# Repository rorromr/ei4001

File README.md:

# EI4001

## Torso lift mechanism

## Instalación

# Repositorio

```
git clone https://github.com/rorromr/ei4001.git
cd ei4001
git submodule init
git submodule update
```
# Librerías Arduino

Para la instalación de librerías se crean enlaces simbolicos en el directorio `~/Arduino/libraries/`.

```
cd ei4001/arduino
./install.sh

```

## Comandos Git

[Guía rápida Git](http://rogerdudler.github.io/git-guide/index.es.html)

### Commandos útiles

* Clonar repositorio: `git clone user@ip_server:repo`
* Crear rama: `git checkout -b nueva_rama`
* Listar ramas: `git branch -a`
* Bajar rama: `git pull origin nombre_rama`
* Crear rama local y setear track remoto: `git checkout -t origin/nombre_rama`
* Borrar rama local (-D para forzar): `git branch -d nombre_rama`
* Borrar rama remota: `git push origin :nombre-rama`
* Subir nueva rama con tracking: `git push -u origin rama`
* Actualizar lista de ramas: `git remote update origin --prune`
* Borrar rama local: `git branch -d rama`
* Borrar rama remota: `git push origin --delete rama`

## Markdown

* [Markdown basics](https://help.github.com/articles/markdown-basics/)
* [Mastering Markdown](https://guides.github.com/features/mastering-markdown/)

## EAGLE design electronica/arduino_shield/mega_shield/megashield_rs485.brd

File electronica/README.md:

# EI4001

## Torso lift mechanism

Archivos de diseño electrónico.

## Puente H

Puente H basado en MOSFET de potencia IRF2804 usando drivers
IR2110.

## Sitios web

* [Calculo de ancho de pistas](http://www.desmith.net/NMdS/Electronics/TraceWidth.html)
* [Ejemplos puente H](http://tahmidmc.blogspot.cl/2013/01/using-high-low-side-driver-ir2110-with.html)

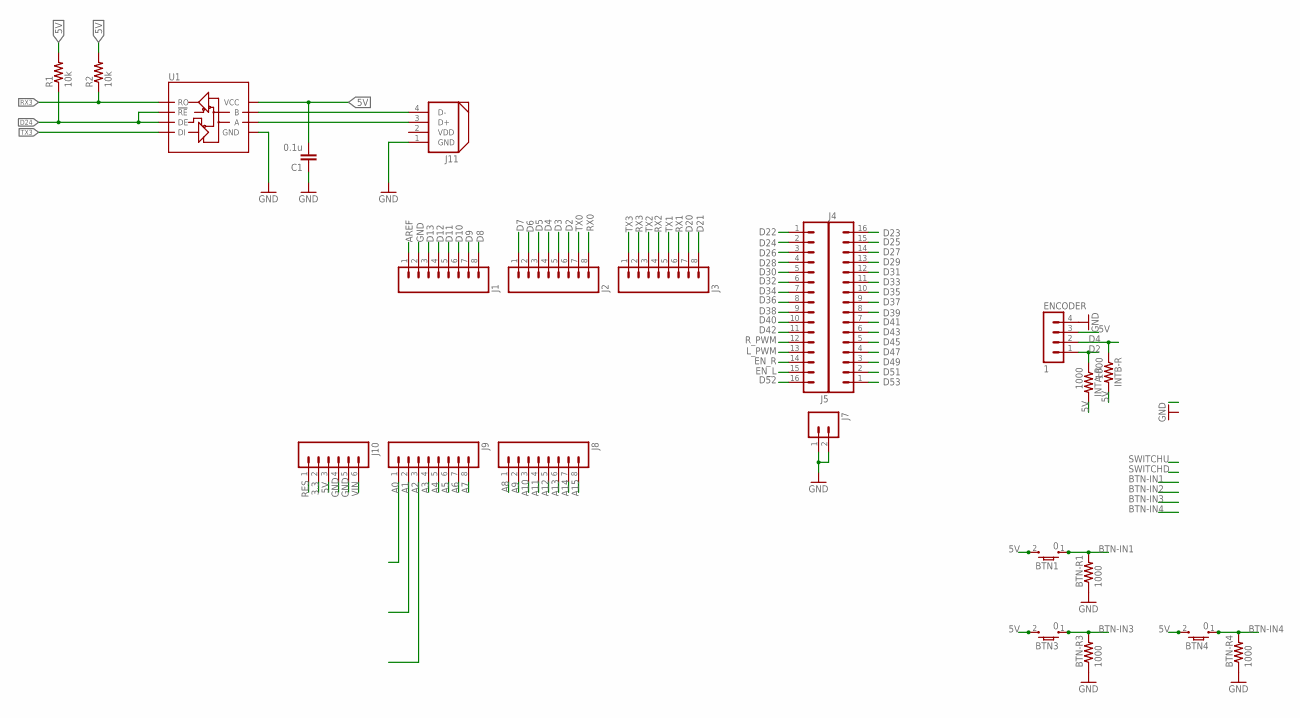
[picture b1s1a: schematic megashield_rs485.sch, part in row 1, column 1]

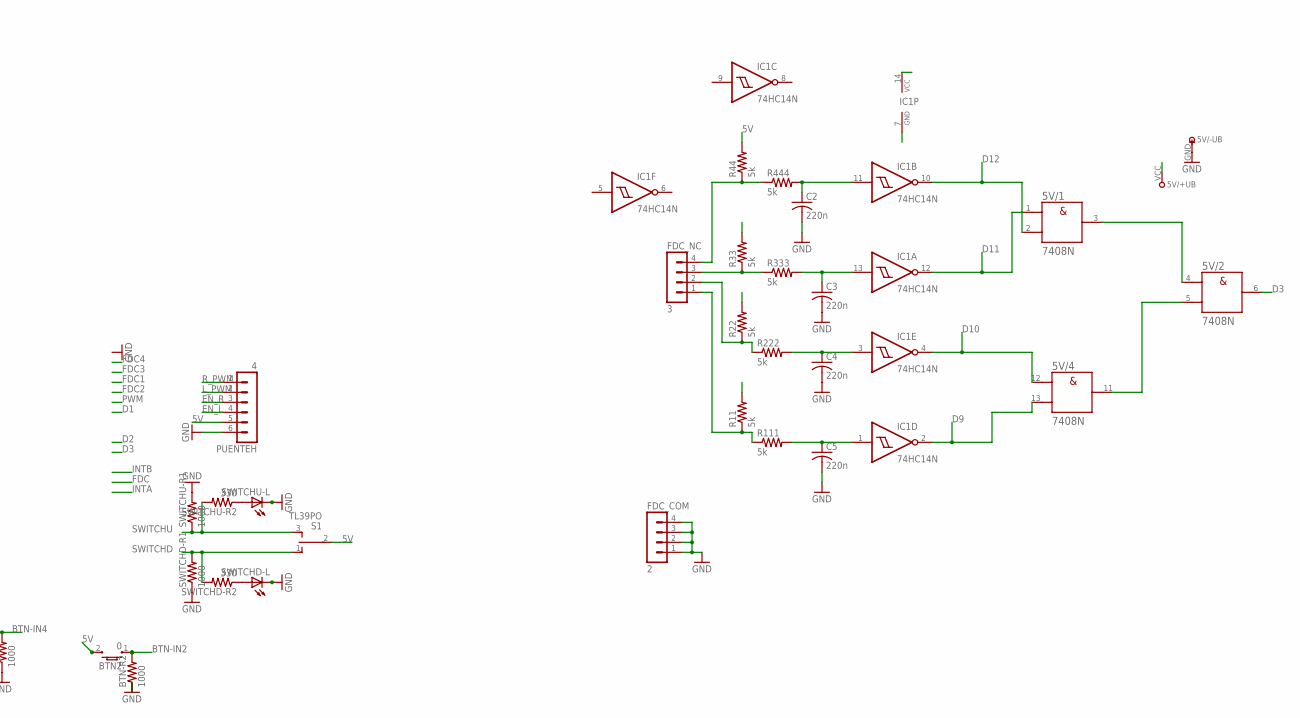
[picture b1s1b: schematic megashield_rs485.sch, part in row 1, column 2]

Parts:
5V: 7408N; DIL14
BTN1, BTN2, BTN3, BTN4: 0; TL3303_J
BTN-R1, BTN-R2, BTN-R3, BTN-R4: 1000; 0204/7
C1: 0.1u; CAP-PTH-SMALL
C2, C3, C4, C5: 220n; C025-030X050
ENCODER: 1; MA04-1
FDC_COM: 2; MA04-1
FDC_NC: 3; MA04-1
IC1: 74HC14N; DIL14
INTA-R: 1000; 0204/7
INTB-R: 1000; 0204/7
J1, J2, J3, J8, J9: M08LONGPADS; 1X08_LONGPADS
J4, J5: M16PTH; 1X16
J7: M02PTH; 1X02
J10: M06LONGPADS; 1X06_LONGPADS
J11: DYNAMIXEL_RS485; DYNAMIXEL_SPOX_04
PUENTEH: 4; MA06-1
R1, R2: 10k; AXIAL-0.4
R11, R22, R33, R44, R111, R222, R333, R444: 5k; 0204/7
S1: TL39PO; TL3XPO
SWITCHD-L: LED_ELD260; LED_LD260
SWITCHD-R1: 1000; 0204/7
SWITCHD-R2: 330; 0204/7
SWITCHU-L: LED_ELD260; LED_LD260
SWITCHU-R1: 1000; 0204/7
SWITCHU-R2: 330; 0204/7
U1: RS485; DIL08

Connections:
3.3: J10.2
5V: 5V.VCC (+UB), BTN1.2, BTN2.2, BTN3.2, BTN4.2, C1.2, ENCODER.3, IC1.14 (VCC), INTA-R.2, INTB-R.2, J10.3, PUENTEH.5, R1.P$2 (2), R2.P$2 (2), R11.2, R22.2, R33.2, R44.2, S1.2, U1.8 (VCC)
A0: J9.1
A1: J9.2
A2: J9.3
A3: J9.4
A4: J9.5
A5: J9.6
A6: J9.7
A7: J9.8
A8: J8.1
A9: J8.2
A10: J8.3
A11: J8.4
A12: J8.5
A13: J8.6
A14: J8.7
A15: J8.8
AREF: J1.1
BTN-IN1: BTN1.1, BTN-R1.2
BTN-IN2: BTN2.1, BTN-R2.2
BTN-IN3: BTN3.1, BTN-R3.2
BTN-IN4: BTN4.1, BTN-R4.2
D2: ENCODER.1, INTA-R.1, J2.6
D3: 5V.6 (Y), J2.5
D4: ENCODER.2, INTB-R.1, J2.4
D5: J2.3
D6: J2.2
D7: J2.1
D8: J1.8
D9: 5V.13 (B), IC1.2 (O), J1.7
D10: 5V.12 (A), IC1.4 (O), J1.6
D11: 5V.1 (A), IC1.12 (O), J1.5
D12: 5V.2 (B), IC1.10 (O), J1.4
D13: J1.3
D20: J3.7
D21: J3.8
D22: J5.1
D23: J4.16
D24: J5.2, R1.P$1 (1), U1.2 (!RE), U1.3 (DE)
D25: J4.15
D26: J5.3
D27: J4.14
D28: J5.4
D29: J4.13
D30: J5.5
D31: J4.12
D32: J5.6
D33: J4.11
D34: J5.7
D35: J4.10
D36: J5.8
D37: J4.9
D38: J5.9
D39: J4.8
D40: J5.10
D41: J4.7
D42: J5.11
D43: J4.6
D45: J4.5
D47: J4.4
D49: J4.3
D51: J4.2
D52: J5.16
D53: J4.1
EN_L: J5.15, PUENTEH.4
EN_R: J5.14, PUENTEH.3
GND: 5V.GND (-UB), BTN-R1.1, BTN-R2.1, BTN-R3.1, BTN-R4.1, C1.1, C2.2, C3.2, C4.2, C5.2, ENCODER.4, FDC_COM.1, FDC_COM.2, FDC_COM.3, FDC_COM.4, IC1.7 (GND), J1.2, J7.1, J7.2, J10.4, J10.5, J11.1 (GND), PUENTEH.6, SWITCHD-L.K (C), SWITCHD-R1.1, SWITCHU-L.K (C), SWITCHU-R1.2, U1.5 (GND)
L_PWM: J5.13, PUENTEH.2
unnamed: J11.3 (D+), U1.6 (A)
unnamed: J11.4 (D-), U1.7 (B)
unnamed: SWITCHU-L.A, SWITCHU-R2.1
unnamed: SWITCHD-L.A, SWITCHD-R2.1
unnamed: FDC_NC.4, R44.1, R444.1
unnamed: FDC_NC.3, R33.1, R333.1
unnamed: C2.1, IC1.11 (I), R444.2
unnamed: C3.1, IC1.13 (I), R333.2
unnamed: FDC_NC.2, R22.1, R222.1
unnamed: C4.1, IC1.3 (I), R222.2
unnamed: FDC_NC.1, R11.1, R111.1
unnamed: C5.1, IC1.1 (I), R111.2
unnamed: 5V.5 (B), 5V.11 (Y)
unnamed: 5V.3 (Y), 5V.4 (A)
RES: J10.1
RX0: J2.8
RX1: J3.6
RX2: J3.4
RX3: J3.2, R2.P$1 (1), U1.1 (RO)
R_PWM: J5.12, PUENTEH.1
SWITCHD: S1.1 (O), SWITCHD-R1.2, SWITCHD-R2.2
SWITCHU: S1.3 (S), SWITCHU-R1.1, SWITCHU-R2.2
TX0: J2.7
TX1: J3.5
TX2: J3.3
TX3: J3.1, U1.4 (DI)
VDD: J11.2 (VDD)
VIN: J10.6

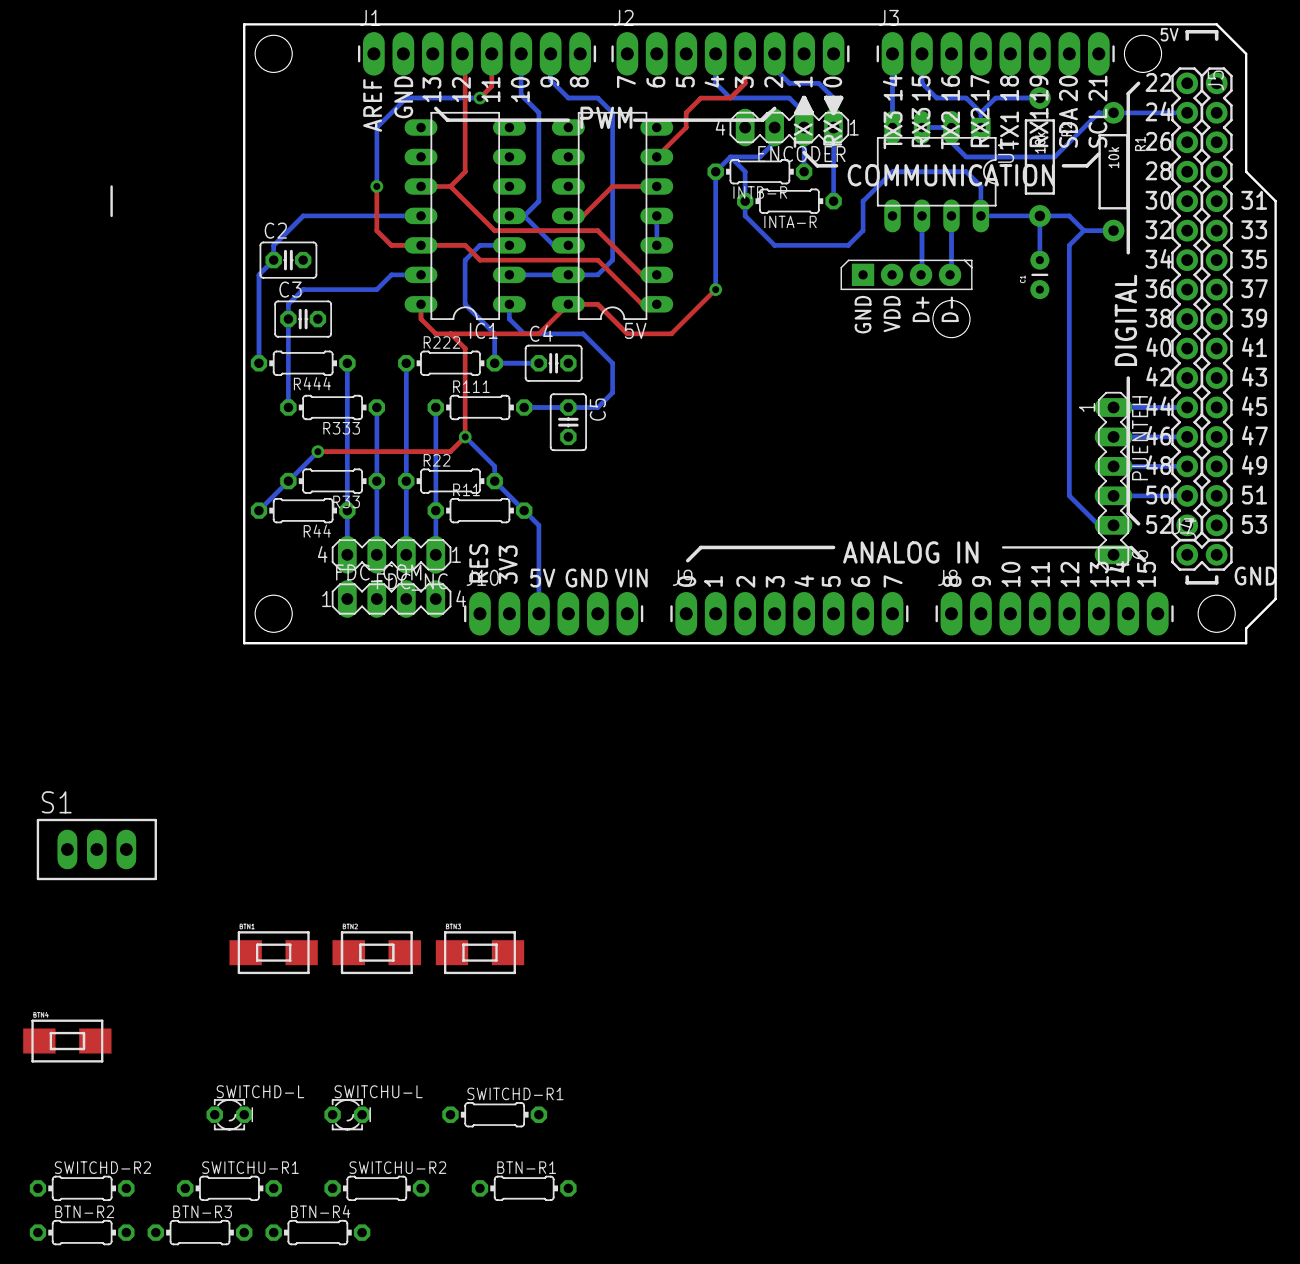
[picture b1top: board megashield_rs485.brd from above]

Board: 2 copper layers, 88.9 x 53.3 mm, 49 parts (0 on the bottom side), 36 nets.

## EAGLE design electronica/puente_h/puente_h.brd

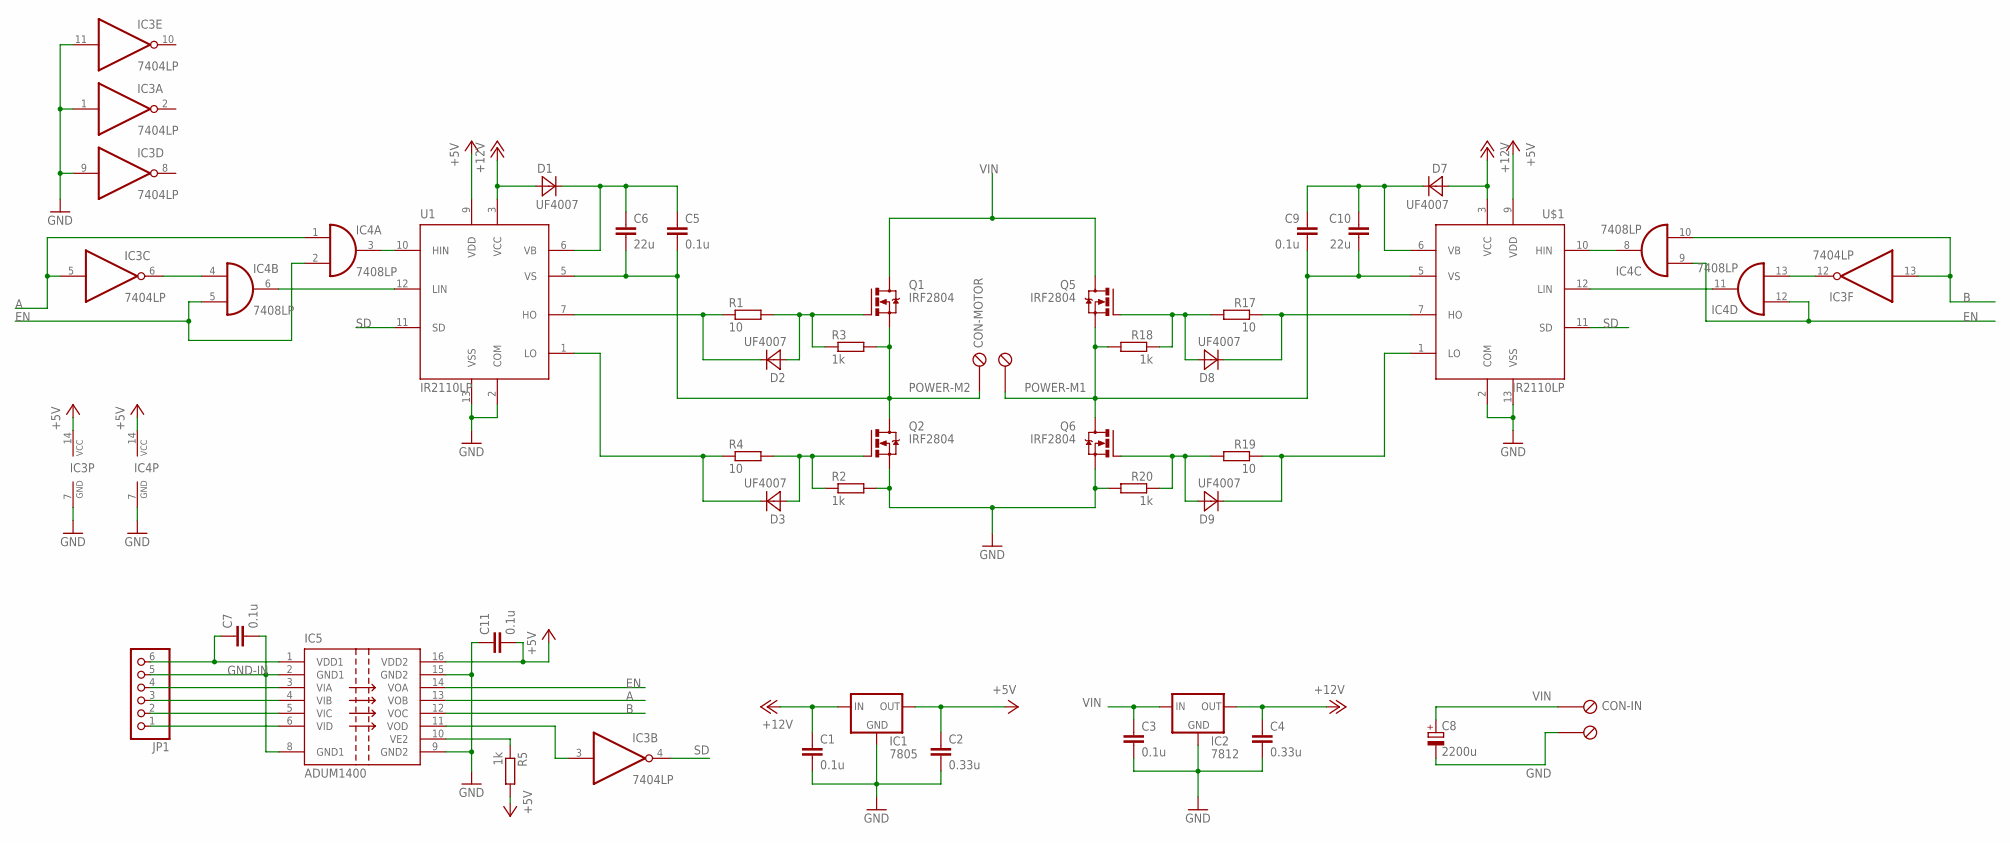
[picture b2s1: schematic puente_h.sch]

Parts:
C1, C3, C5, C9: 0.1u; C050-025X075
C2, C4: 0.33u; C025-025X050
C6, C10: 22u; C025-025X050
C7, C11: 0.1u; C3216
C8: 2200u; E7,5-16
CON-IN: METALTEX-2
CON-MOTOR: METALTEX-2
D1, D2, D3, D7, D8, D9: UF4007
IC1: 7805; 78XXS
IC2: 7812; 78XXS
IC3: 7404LP; IR2110-LP
IC4: 7408LP; IR2110-LP
IC5: ADUM1400; SO16W
JP1: PINHD-1X6; 1X06
Q1, Q2, Q5, Q6: IRF2804
R1, R4, R17, R19: 10; 0207/12
R2, R3, R5, R18, R20: 1k; 0207/12
U1: IR2110LP; IR2110-LP
U$1: IR2110LP; IR2110-LP

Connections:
+5V: C2.1, C11.2, IC1.OUT, IC3.14 (VCC), IC4.14 (VCC), IC5.16 (VDD2), R5.2, U1.9 (VDD), U$1.9 (VDD)
+12V: C1.1, C4.1, D1.A, D7.A, IC1.IN, IC2.OUT, U1.3 (VCC), U$1.3 (VCC)
A: IC3.5 (I), IC4.1 (I0), IC5.13 (VOB)
B: IC3.13 (I), IC4.10 (I1), IC5.12 (VOC)
EN: IC4.2 (I1), IC4.5 (I1), IC4.9 (I0), IC4.12 (I0), IC5.14 (VOA)
GND: C1.2, C2.2, C3.2, C4.2, C8.-, C11.1, CON-IN.P2, IC1.GND, IC2.GND, IC3.1 (I), IC3.7 (GND), IC3.9 (I), IC3.11 (I), IC4.7 (GND), IC5.9 (GND2), IC5.15 (GND2), Q2.S, Q6.S, R2.2, R20.2, U1.2 (COM), U1.13 (VSS), U$1.2 (COM), U$1.13 (VSS)
GND-IN: C7.2, IC5.2 (GND1), IC5.8 (GND1), JP1.5
unnamed: C5.1, C6.1, D1.C, U1.6 (VB)
unnamed: D2.C, R1.1, U1.7 (HO)
unnamed: D2.A, Q1.G, R1.2, R3.1
unnamed: D3.C, R4.1, U1.1 (LO)
unnamed: D3.A, Q2.G, R2.1, R4.2
unnamed: IC4.8 (O), U$1.10 (HIN)
unnamed: IC3.6 (O), IC4.4 (I0)
unnamed: IC4.3 (O), U1.10 (HIN)
unnamed: IC4.6 (O), U1.12 (LIN)
unnamed: IC5.5 (VIC), JP1.2
unnamed: IC5.10 (VE2), R5.1
unnamed: IC3.12 (O), IC4.13 (I1)
unnamed: IC3.3 (I), IC5.11 (VOD)
unnamed: IC4.11 (O), U$1.12 (LIN)
unnamed: IC5.6 (VID), JP1.1
unnamed: IC5.4 (VIB), JP1.3
unnamed: IC5.3 (VIA), JP1.4
unnamed: C7.1, IC5.1 (VDD1), JP1.6
unnamed: C9.1, C10.1, D7.C, U$1.6 (VB)
unnamed: D8.C, R17.1, U$1.7 (HO)
unnamed: D8.A, Q5.G, R17.2, R18.1
unnamed: D9.C, R19.1, U$1.1 (LO)
unnamed: D9.A, Q6.G, R19.2, R20.1
POWER-M1: C9.2, C10.2, CON-MOTOR.P2, Q5.S, Q6.D, R18.2, U$1.5 (VS)
POWER-M2: C5.2, C6.2, CON-MOTOR.P1, Q1.S, Q2.D, R3.2, U1.5 (VS)
SD: IC3.4 (O), U1.11 (SD), U$1.11 (SD)
VIN: C3.1, C8.+, CON-IN.P1, IC2.IN, Q1.D, Q5.D

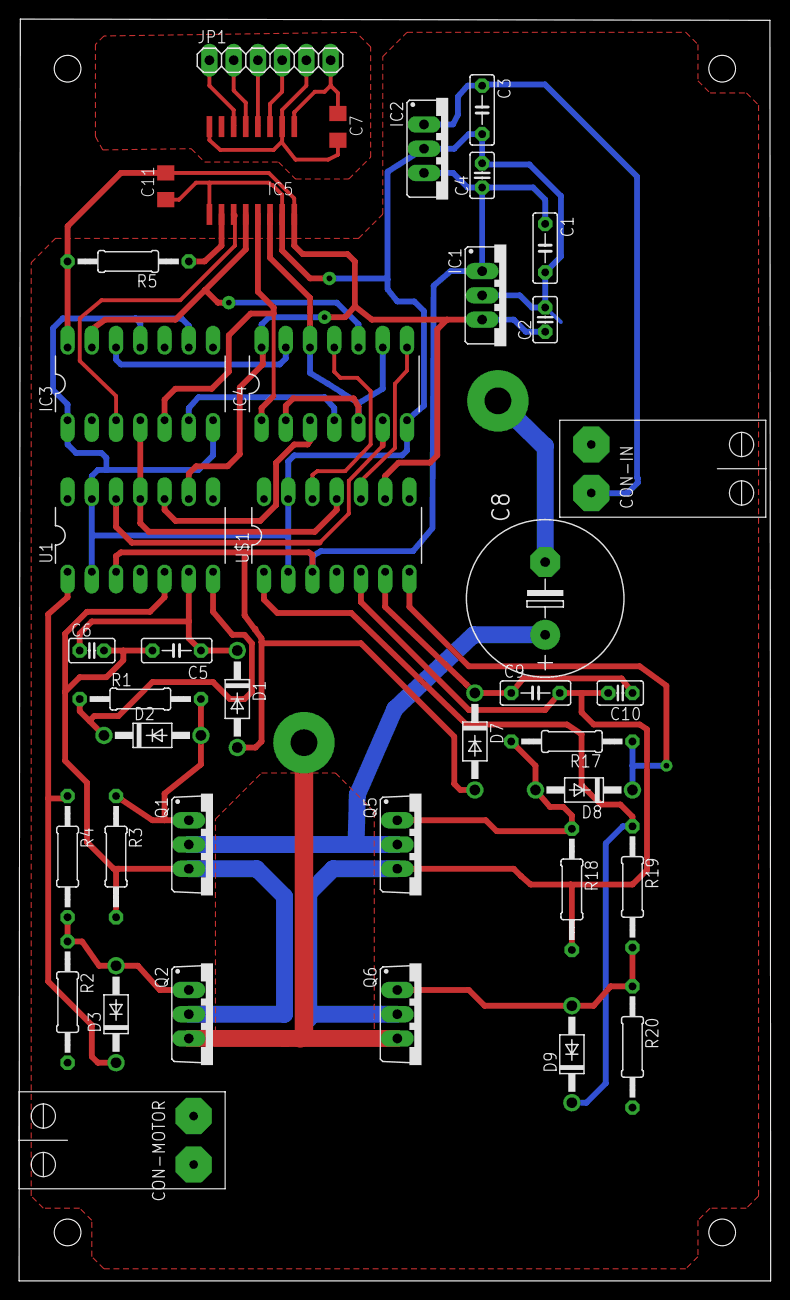
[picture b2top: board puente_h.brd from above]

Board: 2 copper layers, 78.7 x 132.2 mm, 40 parts (0 on the bottom side), 34 nets.

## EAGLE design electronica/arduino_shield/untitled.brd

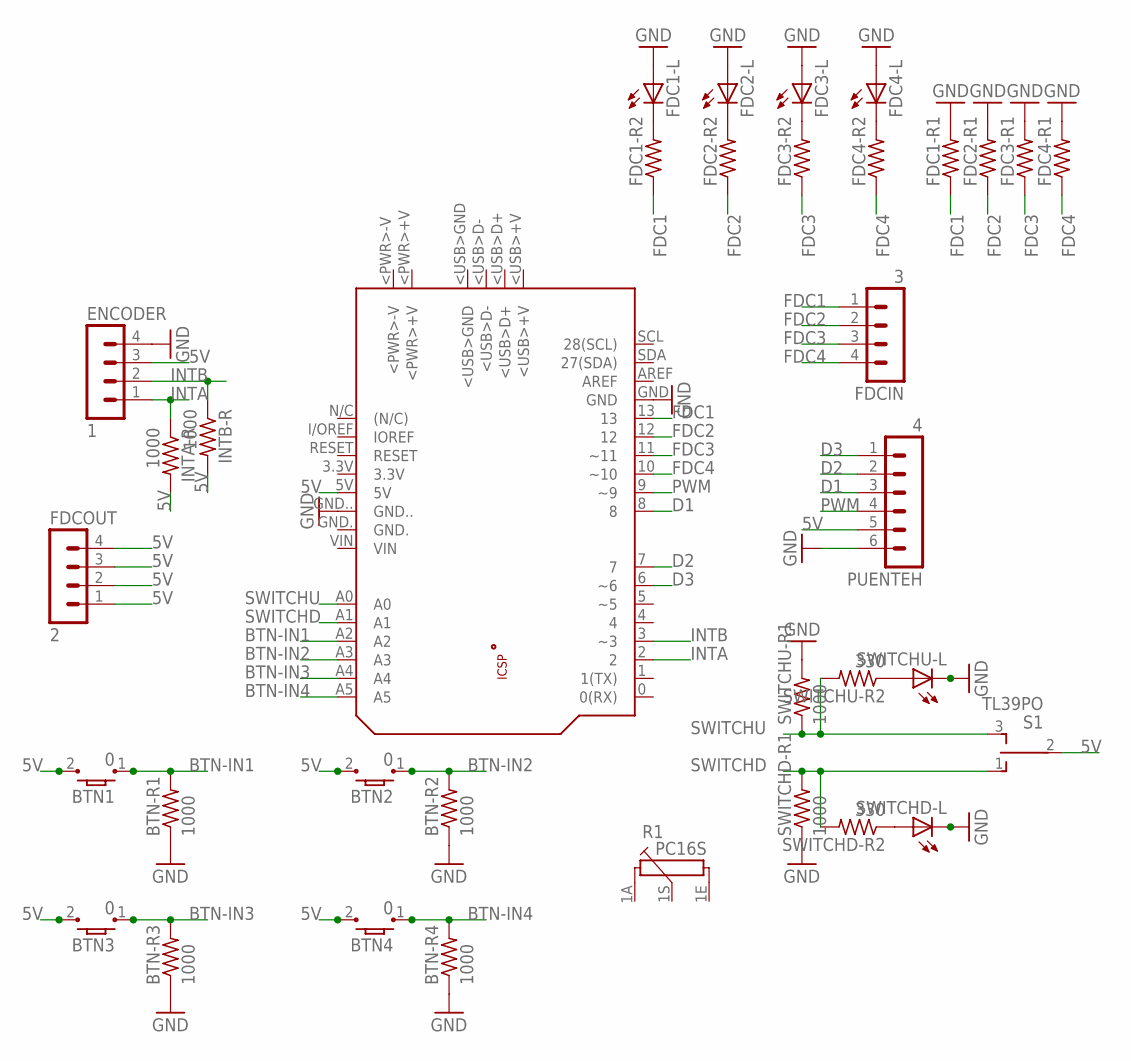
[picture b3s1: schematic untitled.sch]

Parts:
BTN1, BTN2, BTN3, BTN4: 0; TL3303_J
BTN-R1, BTN-R2, BTN-R3, BTN-R4: 1000; 0204/7
ENCODER: 1; MA04-1
FDC1-L, FDC2-L, FDC3-L, FDC4-L: LED_ELD260; LED_LD260
FDC1-R1, FDC1-R2, FDC2-R1, FDC2-R2, FDC3-R1, FDC3-R2, FDC4-R1, FDC4-R2: R-US_0204/7; 0204/7
FDCIN: 3; MA04-1
FDCOUT: 2; MA04-1
INTA-R: 1000; 0204/7
INTB-R: 1000; 0204/7
PCB1: ARDUINO_UNO
PUENTEH: 4; MA06-1
R1: PC16S
S1: TL39PO; TL3XPO
SWITCHD-L: LED_ELD260; LED_LD260
SWITCHD-R1: 1000; 0204/7
SWITCHD-R2: 330; 0204/7
SWITCHU-L: LED_ELD260; LED_LD260
SWITCHU-R1: 1000; 0204/7
SWITCHU-R2: 330; 0204/7

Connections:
5V: BTN1.2, BTN2.2, BTN3.2, BTN4.2, ENCODER.3, FDCOUT.1, FDCOUT.2, FDCOUT.3, FDCOUT.4, INTA-R.2, INTB-R.2, PCB1.5V, PUENTEH.5, S1.2
BTN-IN1: BTN1.1, BTN-R1.2, PCB1.A2
BTN-IN2: BTN2.1, BTN-R2.2, PCB1.A3
BTN-IN3: BTN3.1, BTN-R3.2, PCB1.A4
BTN-IN4: BTN4.1, BTN-R4.2, PCB1.A5
D1: PCB1.8, PUENTEH.3
D2: PCB1.7, PUENTEH.2
D3: PCB1.6 (~6), PUENTEH.1
FDC1: FDC1-R1.1, FDC1-R2.1, FDCIN.1, PCB1.13
FDC2: FDC2-R1.1, FDC2-R2.1, FDCIN.2, PCB1.12
FDC3: FDC3-R1.1, FDC3-R2.1, FDCIN.3, PCB1.11 (~11)
FDC4: FDC4-R1.1, FDC4-R2.1, FDCIN.4, PCB1.10 (~10)
GND: BTN-R1.1, BTN-R2.1, BTN-R3.1, BTN-R4.1, ENCODER.4, FDC1-L.A, FDC1-R1.2, FDC2-L.A, FDC2-R1.2, FDC3-L.A, FDC3-R1.2, FDC4-L.A, FDC4-R1.2, PCB1.GND, PCB1.GND.., PUENTEH.6, SWITCHD-L.K (C), SWITCHD-R1.1, SWITCHU-L.K (C), SWITCHU-R1.2
INTA: ENCODER.1, INTA-R.1, PCB1.2
INTB: ENCODER.2, INTB-R.1, PCB1.3 (~3)
unnamed: FDC1-L.K (C), FDC1-R2.2
unnamed: FDC2-L.K (C), FDC2-R2.2
unnamed: SWITCHU-L.A, SWITCHU-R2.1
unnamed: SWITCHD-L.A, SWITCHD-R2.1
unnamed: FDC3-L.K (C), FDC3-R2.2
unnamed: FDC4-L.K (C), FDC4-R2.2
PWM: PCB1.9 (~9), PUENTEH.4
SWITCHD: PCB1.A1, S1.1 (O), SWITCHD-R1.2, SWITCHD-R2.2
SWITCHU: PCB1.A0, S1.3 (S), SWITCHU-R1.1, SWITCHU-R2.2

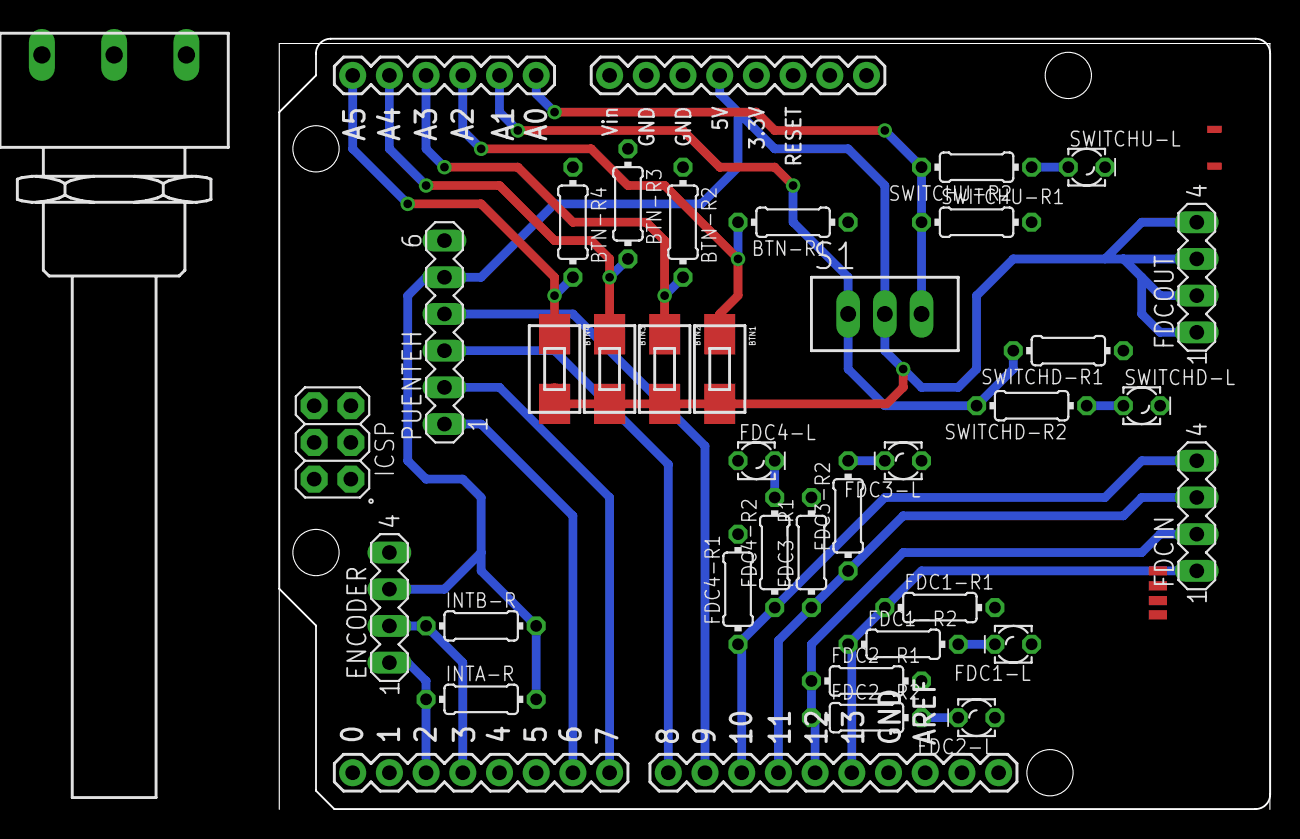
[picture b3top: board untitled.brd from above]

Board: 2 copper layers, 68.6 x 53.3 mm, 35 parts (0 on the bottom side), 24 nets.

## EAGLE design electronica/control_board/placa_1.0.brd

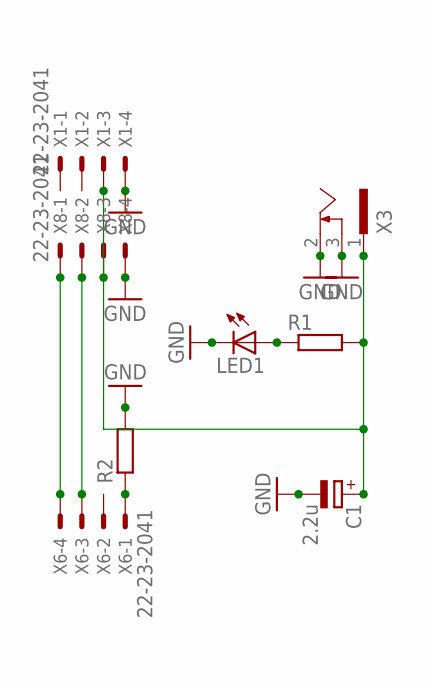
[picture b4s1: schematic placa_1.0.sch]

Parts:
C1: 2.2u; E5-13
LED1: LED_ELD260; LED_LD260
R1, R2: R0207/10; 0207/10
X1, X6, X8: 22-23-2041
X3: SCD-014A; SCD-014-A

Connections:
GND: C1.-, LED1.K (C), R2.2, X1.4, X3.2, X3.3, X8.4
unnamed: R2.1, X6.1
unnamed: X6.4, X8.1
unnamed: X6.3, X8.2
unnamed: LED1.A, R1.1
VCC: C1.+, R1.2, X1.3, X3.1, X8.3

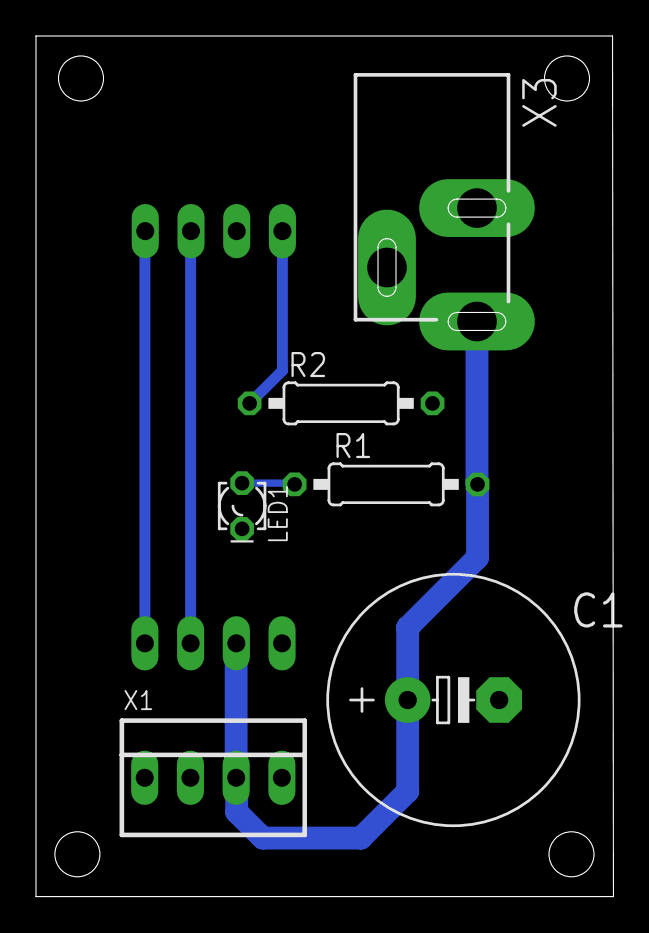
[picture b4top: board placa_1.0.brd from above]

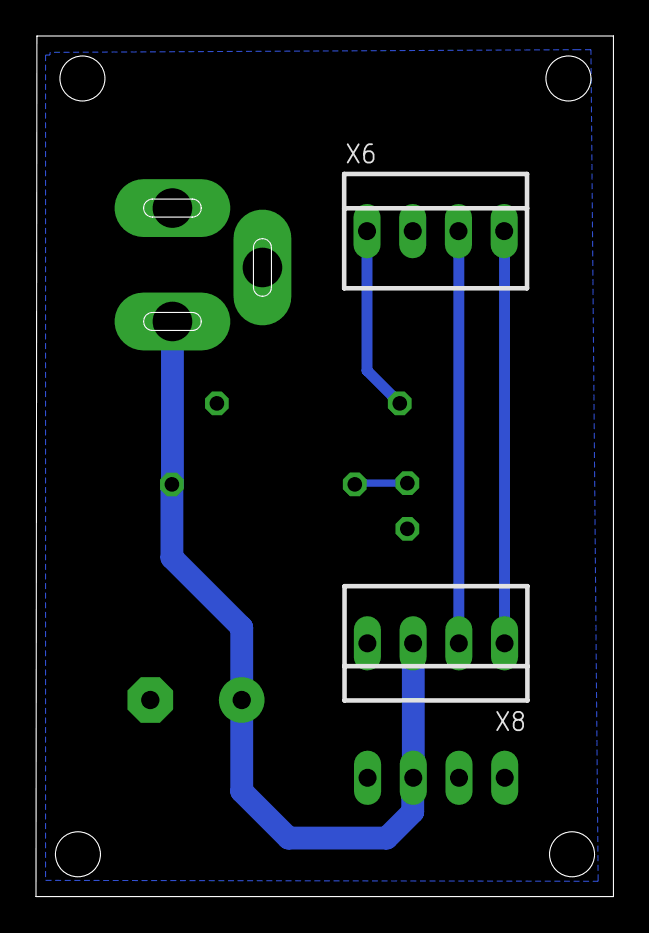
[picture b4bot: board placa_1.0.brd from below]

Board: 2 copper layers, 32.1 x 47.8 mm, 8 parts (2 on the bottom side), 6 nets.

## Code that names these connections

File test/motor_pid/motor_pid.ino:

#include <SimpleEncoder.h>
#include <PID_v1.h>
#include <HBridge.h>

# define MOTOR_B 8
# define MOTOR_A 7
# define MOTOR_PWM 6
# define ENCODER_A 2
# define ENCODER_B 4
# define FDC1 10
# define FDC2 11
# define FDC3 12
# define FDC4 13

// PID
double refP,inputP,outputP; //refP recibe referencia de numero de tics
double KpP = 0.11, KiP=0.05, KdP=0.007;

//controladores
PID pidP(&inputP, &outputP, &refP, KpP, KiP, KdP, DIRECT);

//Clase encoder
Encoder encoder(ENCODER_A, ENCODER_B);

// H bridge class
HBridge hbridge(MOTOR_PWM, MOTOR_A, MOTOR_B);


// Buttons
uint8_t k1 = 0, k1f = 0;
uint8_t k2 = 0, k2f = 0;

void setup(){
  Serial.begin(9600);
  
  hbridge.setPwmFrequency(64); //Pin 6, divido frecuencia base 62,5 Khz por 64
  
  pidP.SetSampleTime(5);
  pidP.SetOutputLimits(-255,255);
  pidP.setDeadZone(30);
  pidP.enableDeadZone(true);
  refP = 5000;

  // Buttons
  pinMode(9, INPUT_PULLUP);
  pinMode(10, INPUT_PULLUP);
}

void loop(){
  inputP = encoder.read();
  pidP.Compute();
  hbridge.set((int16_t) outputP);
  //Serial.print("| Out ");
  //Serial.println(outputP);
  //delay(1);

  // Falling edge K1
  k1f = k1;
  k1 = digitalRead(9);
  if (k1f == HIGH && k1 == LOW) refP += 800;

  // Falling edge K2
  k2f = k2;
  k2 = digitalRead(10);
  if (k2f == HIGH && k2 == LOW) refP -= 800;
}

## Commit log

2015-09-21 hola
2015-09-21 prueba
2015-09-21 directorios
2015-09-22 upd readme
2015-09-22 fix readme
2015-09-28 rs485 test
2015-09-29 libreria arduino compatible
2015-10-02 enconder
2015-10-03 makefiles
2015-10-03 mmap
2015-10-04 eeprom
2015-10-05 encoder+motor
2015-10-05 actualizar
2015-10-05 orden, clases virtuales
2015-10-09 upd dxl
2015-10-09 debug print usando macros
2015-10-15 test encoder
2015-10-16 registros serial
2015-10-16 serial
2015-10-17 mejoras makefile
2015-10-19 device dxl en serial
2015-10-19 serial interrupt
2015-10-20 clase virtual ISR
2015-10-20 pid library
2015-10-21 checksum y test
2015-10-31 comunicacion en ambos sentidos
2015-10-31 mejoras para rs485
2015-10-31 encoder
2015-11-01 controlador
2015-11-02 ordenado
2015-11-02 borrar
2015-11-02 controlista
2015-11-02 upd test
2015-11-02 motor con pid
2015-11-03 algoritmos pid tue
2015-11-04 anti windup
2015-11-04 libreria cambiada
2015-11-05 integrado con ros
2015-11-05 rosserial
2015-11-05 controlador publica y subscribe
2015-11-06 esquematico puente h
2015-11-09 test viernes, esquematico con nuevo optoacoplador
2015-11-09 pads mas largos
2015-11-10 packages con pad mas largos, nuevo pcb
2015-11-10 mejores posiciones
2015-11-13 ruteo mejorado
2015-11-15 ruteo con poligonos
2015-11-16 bender_torso pkg
2015-11-16 torso scripts
2015-11-16 goal generator
2015-11-16 bender torso
2015-11-16 puente h ok
2015-11-16 placas nuevas
2015-11-17 casi encoder
2015-11-17 conectores puente h
2015-11-17 mejoras encoder lib
2015-11-17 encoder 1 ISR
2015-11-17 encoder lib ok
2015-11-18 shield arduino terminado
2015-11-22 correccion de planos, adicion de potenciometro
2015-11-23 nada particular
2015-11-25 package
2015-11-25 script ros_lib
2015-11-25 msg a bender_torso, script para actualizar librerias de ros_lib
2015-11-26 EEPROM y timers
2015-12-02 diagrama para verificar puente h
2015-12-04 actualizacion de esquematico
2015-12-15 fin de carrera, calibracion, dead zone
2015-12-24 lib puente H
2015-12-24 funcion set y mensajes de debug
2015-12-24 integrado con h bridge
2015-12-28 deadzone, pwm en libreria puente H
2015-12-29 botones para cambiar referencia
2015-12-29 test con visualizacion
2015-12-29 test completo
2016-01-05 libreria pid con tipo de datos variable
2016-03-29 Serial ISR para Arduino Mega
2016-03-30 arduino mega registers
2016-04-13 LED test on Arduino Mega
2016-04-14 makefile update
2016-04-14 mmap with uint8_t type
2016-04-15 Access struct
2016-04-20 Access type for variables
2016-04-20 MMap with variables
2016-04-20 Test var
2016-04-21 Test mmap
2016-04-21 Led test
2016-04-22 Led example with rs485
2016-04-22 LED state machine fix
2016-04-23 Test receive
2016-04-23 Test LED controller with ROS
2016-04-23 LED exmaple
2016-04-24 Add SerialDXL submodule
2016-04-24 Update SerialDXL
2016-04-24 Update instalation instructions
2016-04-24 Update install instructions
2016-04-27 test fin de carrera
2016-05-09 Fdc ready
2016-06-03 placa
2016-06-04 test malo
2016-06-04 test fdc
2016-06-04 gitignore for python files
2016-06-07 state machine
2016-06-08 calibracion y avance de maquina estado
2016-06-10 ahora si
2016-06-14 Torso controller using Dynamixel protocol
2016-09-05 relanzamiento torso
2016-09-07 Inicio de dinamixalizacion de Torso
2016-09-07 TorsoController + StateMachine
2016-09-07 no me dejo subirlo al git de SerialDXL, asi que aca va con FLoat32
2016-09-13 mapeo completo, timer para llamar funcion update
2016-09-14 avances state machine
2016-09-15 Mejora en estado de emergencia
2016-09-15 falto agregar limites
2016-09-15 Test
2016-09-28 Update serial dxl
2016-09-28 Add LedTimer test
2016-09-30 placa mega
2016-09-30 Fix timmer on Led test
2016-09-30 double to float
2016-10-06 Test read position
2016-10-06 Fix control table
2016-10-06 Functional test TorsoController
2016-10-06 Fix control table, high level interface
2016-10-11 Documentation for torso controller
2016-10-11 Fix linter warnings
2016-10-11 Parabolic trajectory generation example
2016-10-19 PID gains, PWM frequency
2016-10-19 Trajectory generation
2016-11-09 Encoder test at 6KHz
2016-11-09 Stres test on comunication and encoder
2016-11-16 RAW avr example
